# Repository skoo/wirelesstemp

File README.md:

wirelesstemp
============

wirelesstemp is a wireless temperature sensor with following components:

- Microchip 18f13k22 microcontroller
- Microchip TC77 Thermal sensor with SPI interface
- RF-2400-V03 RF transmitter
- TPS61221 low input voltage boost converter
- 1.5 AAA battery

This 1.5V AAA battery operated temperature sensor sends measurement once each 65.5 seconds.
Sensor should operate for more than one year based on following measurements/assumptions:

- AAA battery holds 1000mAh.
- Sleep state consumes 90uA/65.5s
- Active state 40mA/15ms.

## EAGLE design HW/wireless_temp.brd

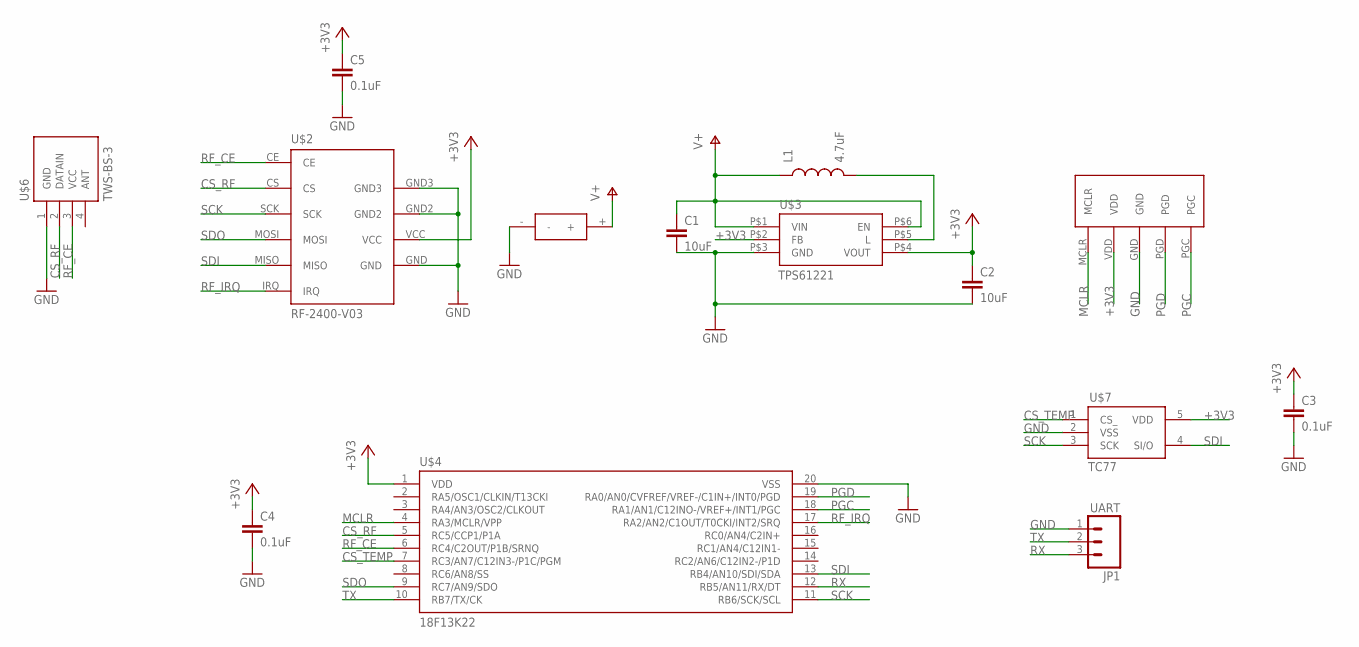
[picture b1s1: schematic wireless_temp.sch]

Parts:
C1, C2: 10uF; 0805
C3, C4, C5: 0.1uF; 0402-CAP
JP1: UART; 1X03
L1: 4.7uF; NR3015T
U$1: BAT_HOLDER; AAA
U$2: RF-2400-V03
U$3: TPS61221; SO6
U$4: 18F13K22; SSOP20
U$5: PIC-ICSP; ICSP
U$6: TWS-BS-3
U$7: TC77; SOT23-5

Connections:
+3V3: C2.1, C3.1, C4.1, C5.1, U$2.VCC, U$3.P$2 (FB), U$3.P$4 (VOUT), U$4.1 (VDD), U$5.VDD, U$7.5 (VDD)
CS_RF: U$2.CS, U$4.5 (RC5/CCP1/P1A), U$6.2 (DATAIN)
CS_TEMP: U$4.7 (RC3/AN7/C12IN3-/P1C/PGM), U$7.1 (CS_)
GND: C1.2, C2.2, C3.2, C4.2, C5.2, JP1.1, U$1.-, U$2.GND, U$2.GND2, U$2.GND3, U$3.P$3 (GND), U$4.20 (VSS), U$5.GND, U$6.1 (GND), U$7.2 (VSS)
MCLR: U$4.4 (RA3/MCLR/VPP), U$5.MCLR
unnamed: L1.P$2 (2), U$3.P$5 (L)
PGC: U$4.18 (RA1/AN1/C12INO-/VREF+/INT1/PGC), U$5.PGC
PGD: U$4.19 (RA0/AN0/CVFREF/VREF-/C1IN+/INT0/PGD), U$5.PGD
RF_CE: U$2.CE, U$4.6 (RC4/C2OUT/P1B/SRNQ), U$6.3 (VCC)
RF_IRQ: U$2.IRQ, U$4.17 (RA2/AN2/C1OUT/T0CKI/INT2/SRQ)
RX: JP1.3, U$4.12 (RB5/AN11/RX/DT)
SCK: U$2.SCK, U$4.11 (RB6/SCK/SCL), U$7.3 (SCK)
SDI: U$2.MISO, U$4.13 (RB4/AN10/SDI/SDA), U$7.4 (SI/O)
SDO: U$2.MOSI, U$4.9 (RC7/AN9/SDO)
TX: JP1.2, U$4.10 (RB7/TX/CK)
V+: C1.1, L1.P$1 (1), U$1.+, U$3.P$1 (VIN), U$3.P$6 (EN)

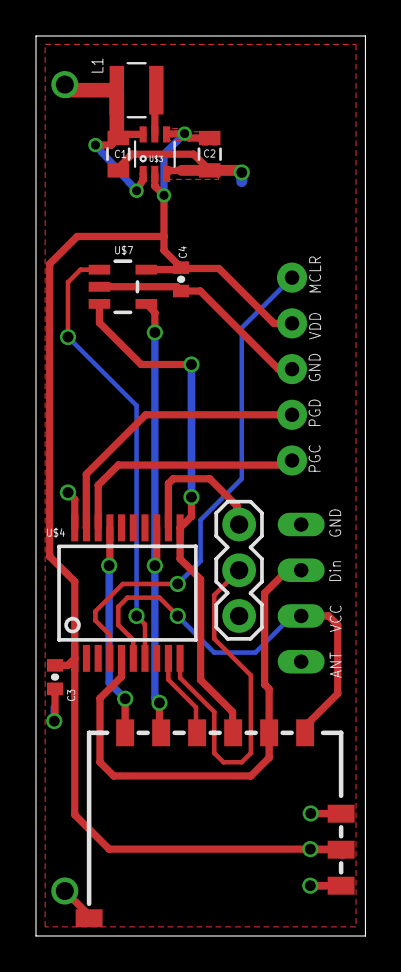
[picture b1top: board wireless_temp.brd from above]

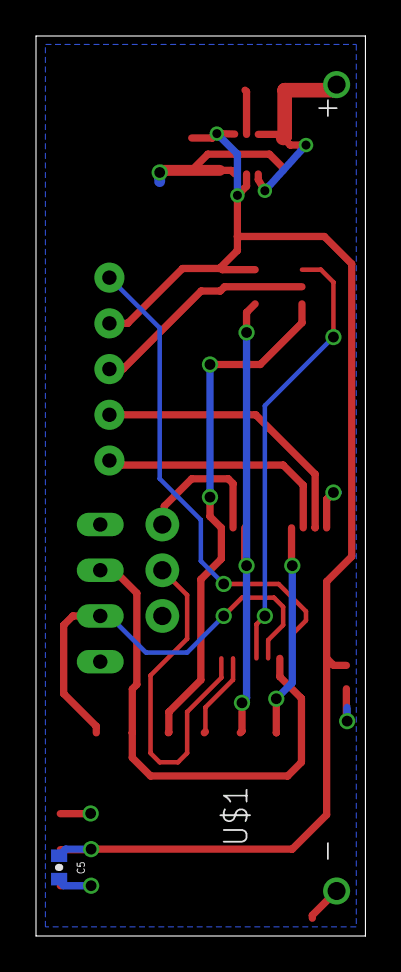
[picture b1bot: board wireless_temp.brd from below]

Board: 2 copper layers, 18.3 x 50.0 mm, 14 parts (2 on the bottom side), 16 nets.

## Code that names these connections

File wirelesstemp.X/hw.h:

#ifndef _HW_H_
#define _HW_H_

#include <p18f13k22.h>
#include <delays.h>

/* TC77 HW config ----------------------------------------------------------- */

#define TC77_CS     PORTCbits.RC3

#define tc77_spi_write(x) \
    SSPBUF = x; \
    while (!SSPSTATbits.BF);

#define tc77_spi_buf    SSPBUF
#define TC77_SDI_TRIS   TRISBbits.TRISB4
#define TC77_SDI_PORT   PORTBbits.RB4

/* BK2421 HW config ----------------------------------------------------------*/

#define BK2421_CS   PORTCbits.RC5
#define BK2421_CE   PORTCbits.RC4
#define BK2421_IRQ  PORTAbits.RA2

#define bk2421_spi_write(x) \
    SSPBUF = x; \
    while (!SSPSTATbits.BF);

#define bk2421_spi_buf    SSPBUF

/* for delays used in bk2421 init */
#define bk2421_delay_ms(x) Delay1KTCYx(x); /* @ 1MHz */
#define bk2421_delay_us(x) Delay10TCYx((x+9)/10); /* @ 1MHz */

#endif /* _HW_H_ */

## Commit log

2012-06-03 Added sources
2012-06-03 Added schematic and board
2012-06-04 Update master

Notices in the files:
parts and their libraries:
SparkFun: Licensing: CC v3.0 Share-Alike You are welcome to use this library for commercial purposes.
